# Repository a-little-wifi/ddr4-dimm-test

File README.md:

# DDR4-dimm-test

I need DDR4 UDIMMs for some PCs I got but I don't feel like buying any so I'll make it myself and harvest chips from a dead 32GB RDIMM (nevermind that's not possible, the RDIMM uses 4-bit chips and I need 8-bit chips)

Resources used:

- https://github.com/vmetodiev/OpenDIMM
- https://github.com/DiodeRed/kicad-footprint-ddr4-dimm
- Random motherboard schematics
- DDR4 specification

for future sodimm version?? :3
- https://github.com/Wallbraker/SODIMM

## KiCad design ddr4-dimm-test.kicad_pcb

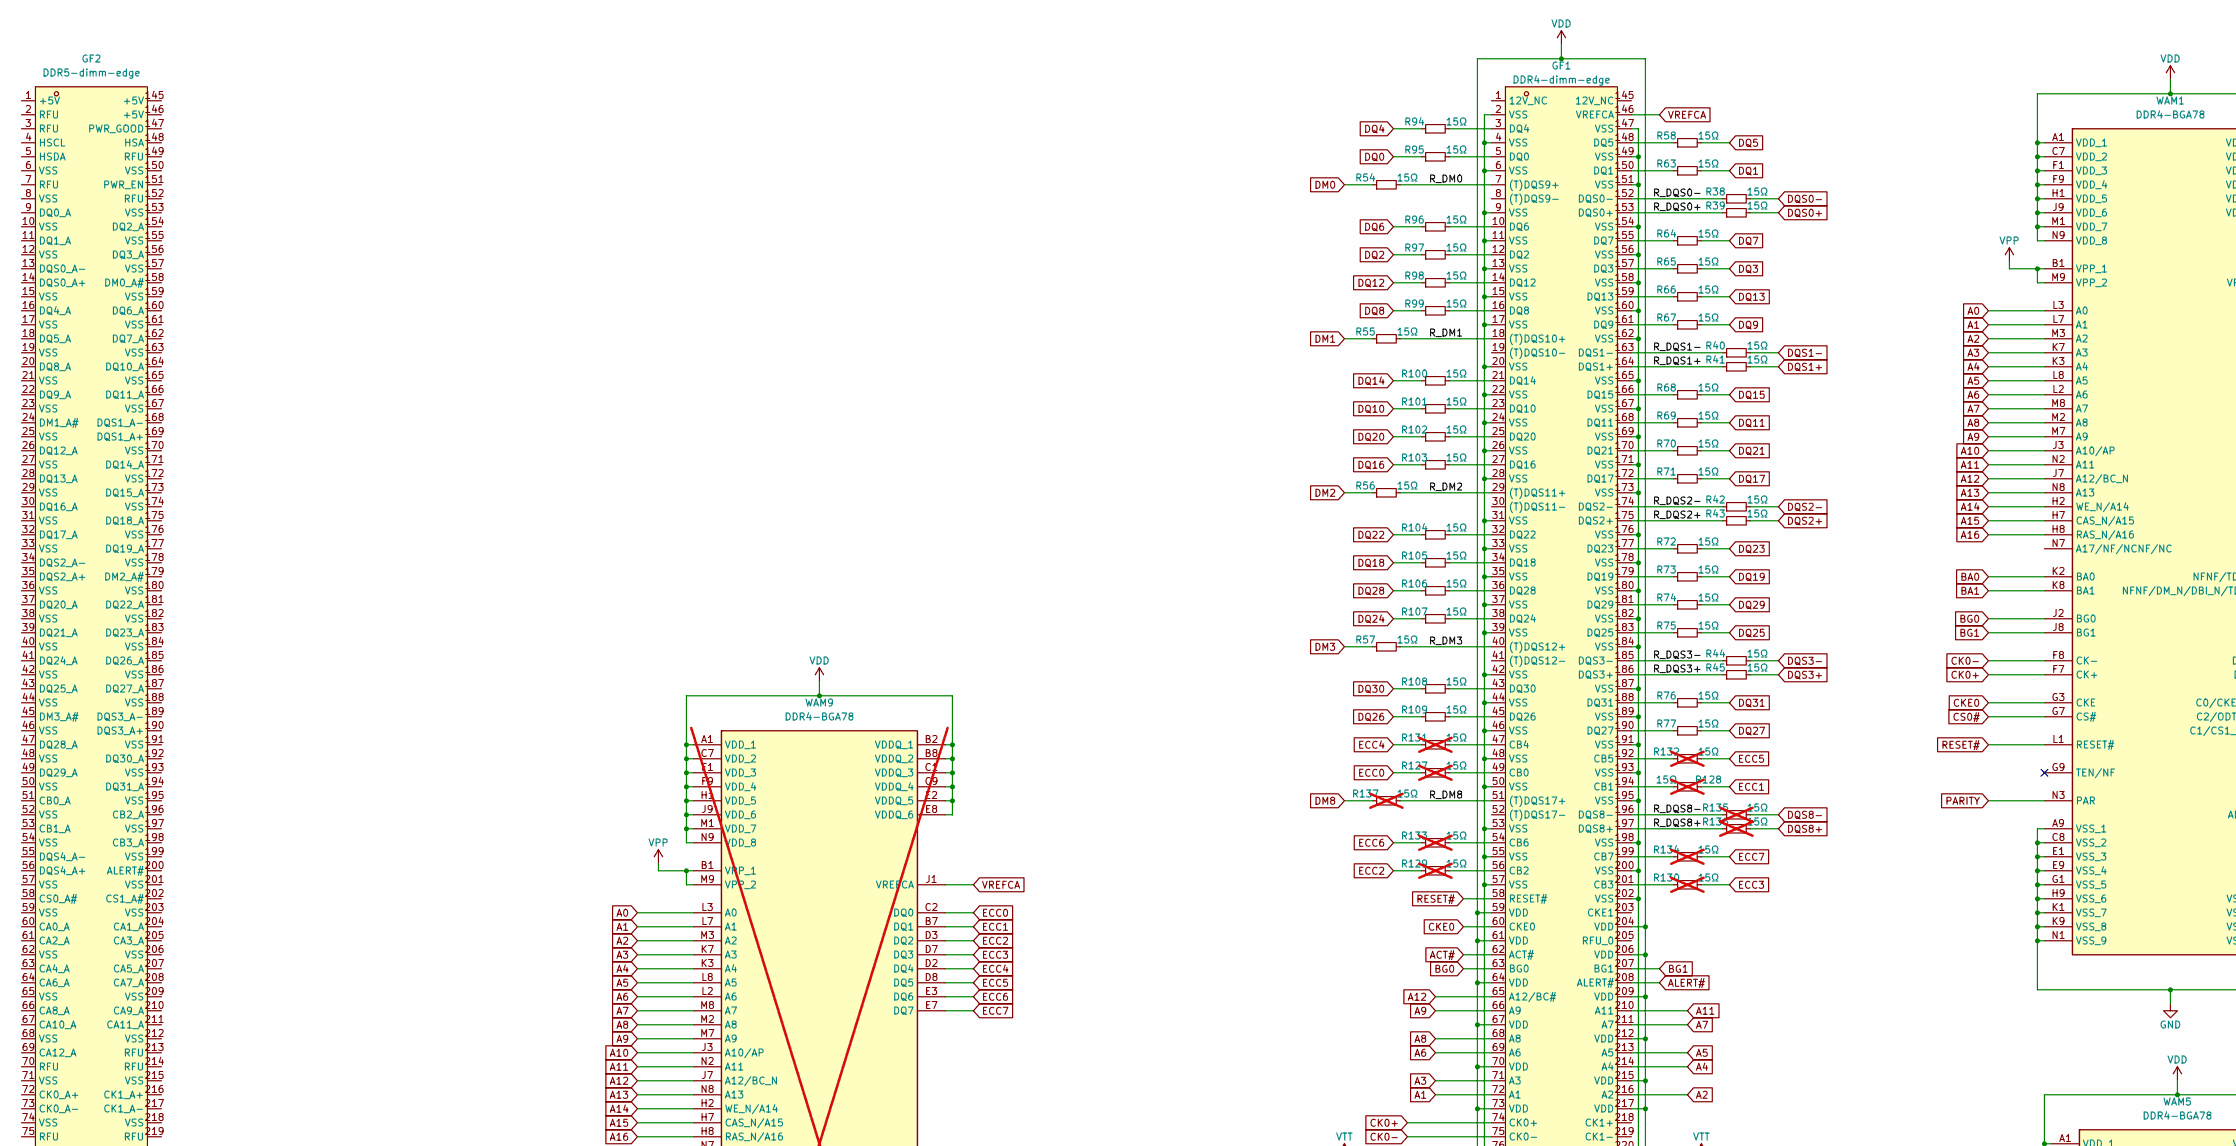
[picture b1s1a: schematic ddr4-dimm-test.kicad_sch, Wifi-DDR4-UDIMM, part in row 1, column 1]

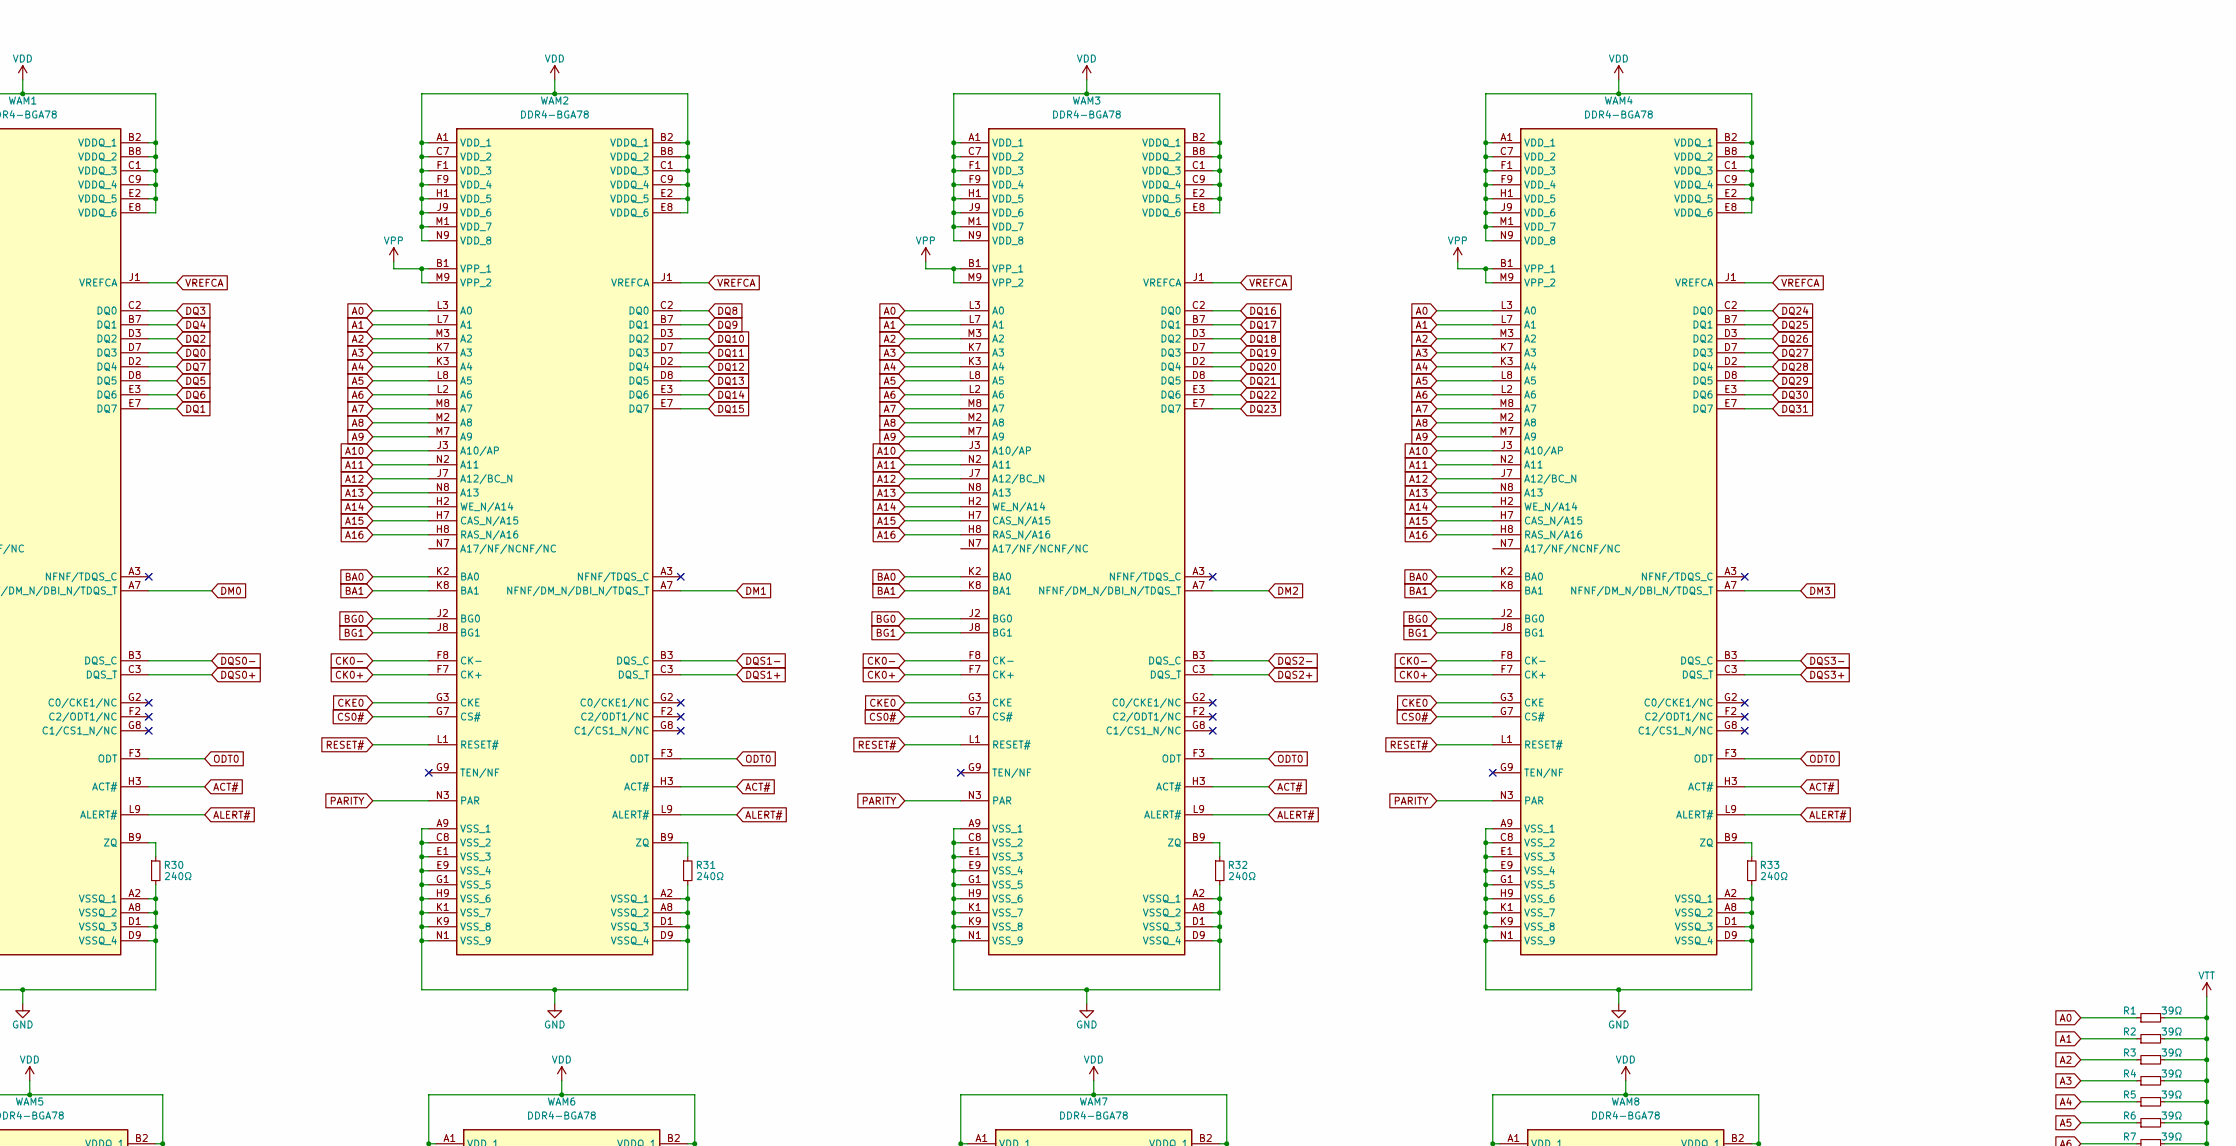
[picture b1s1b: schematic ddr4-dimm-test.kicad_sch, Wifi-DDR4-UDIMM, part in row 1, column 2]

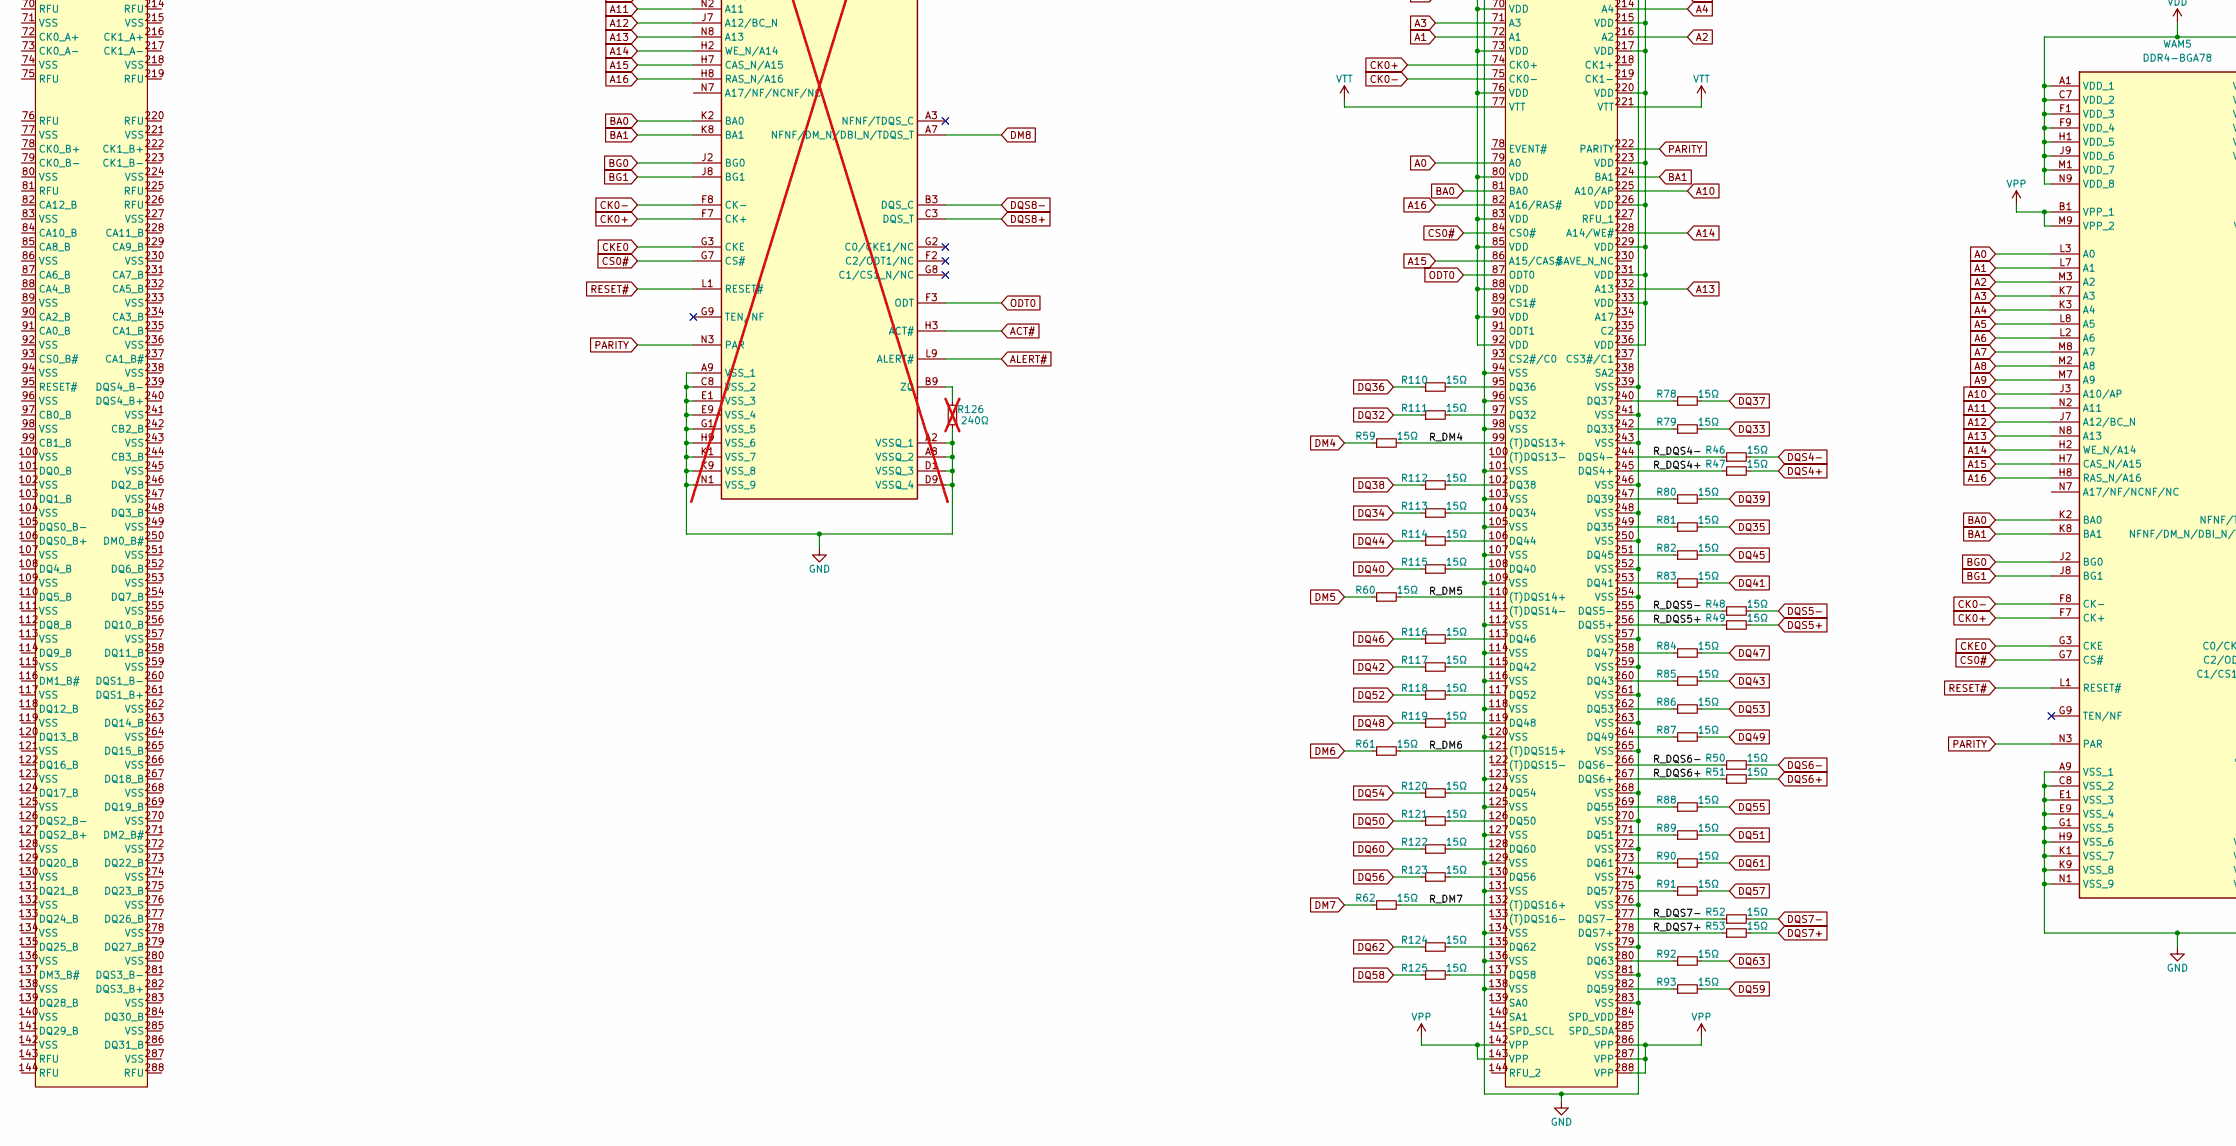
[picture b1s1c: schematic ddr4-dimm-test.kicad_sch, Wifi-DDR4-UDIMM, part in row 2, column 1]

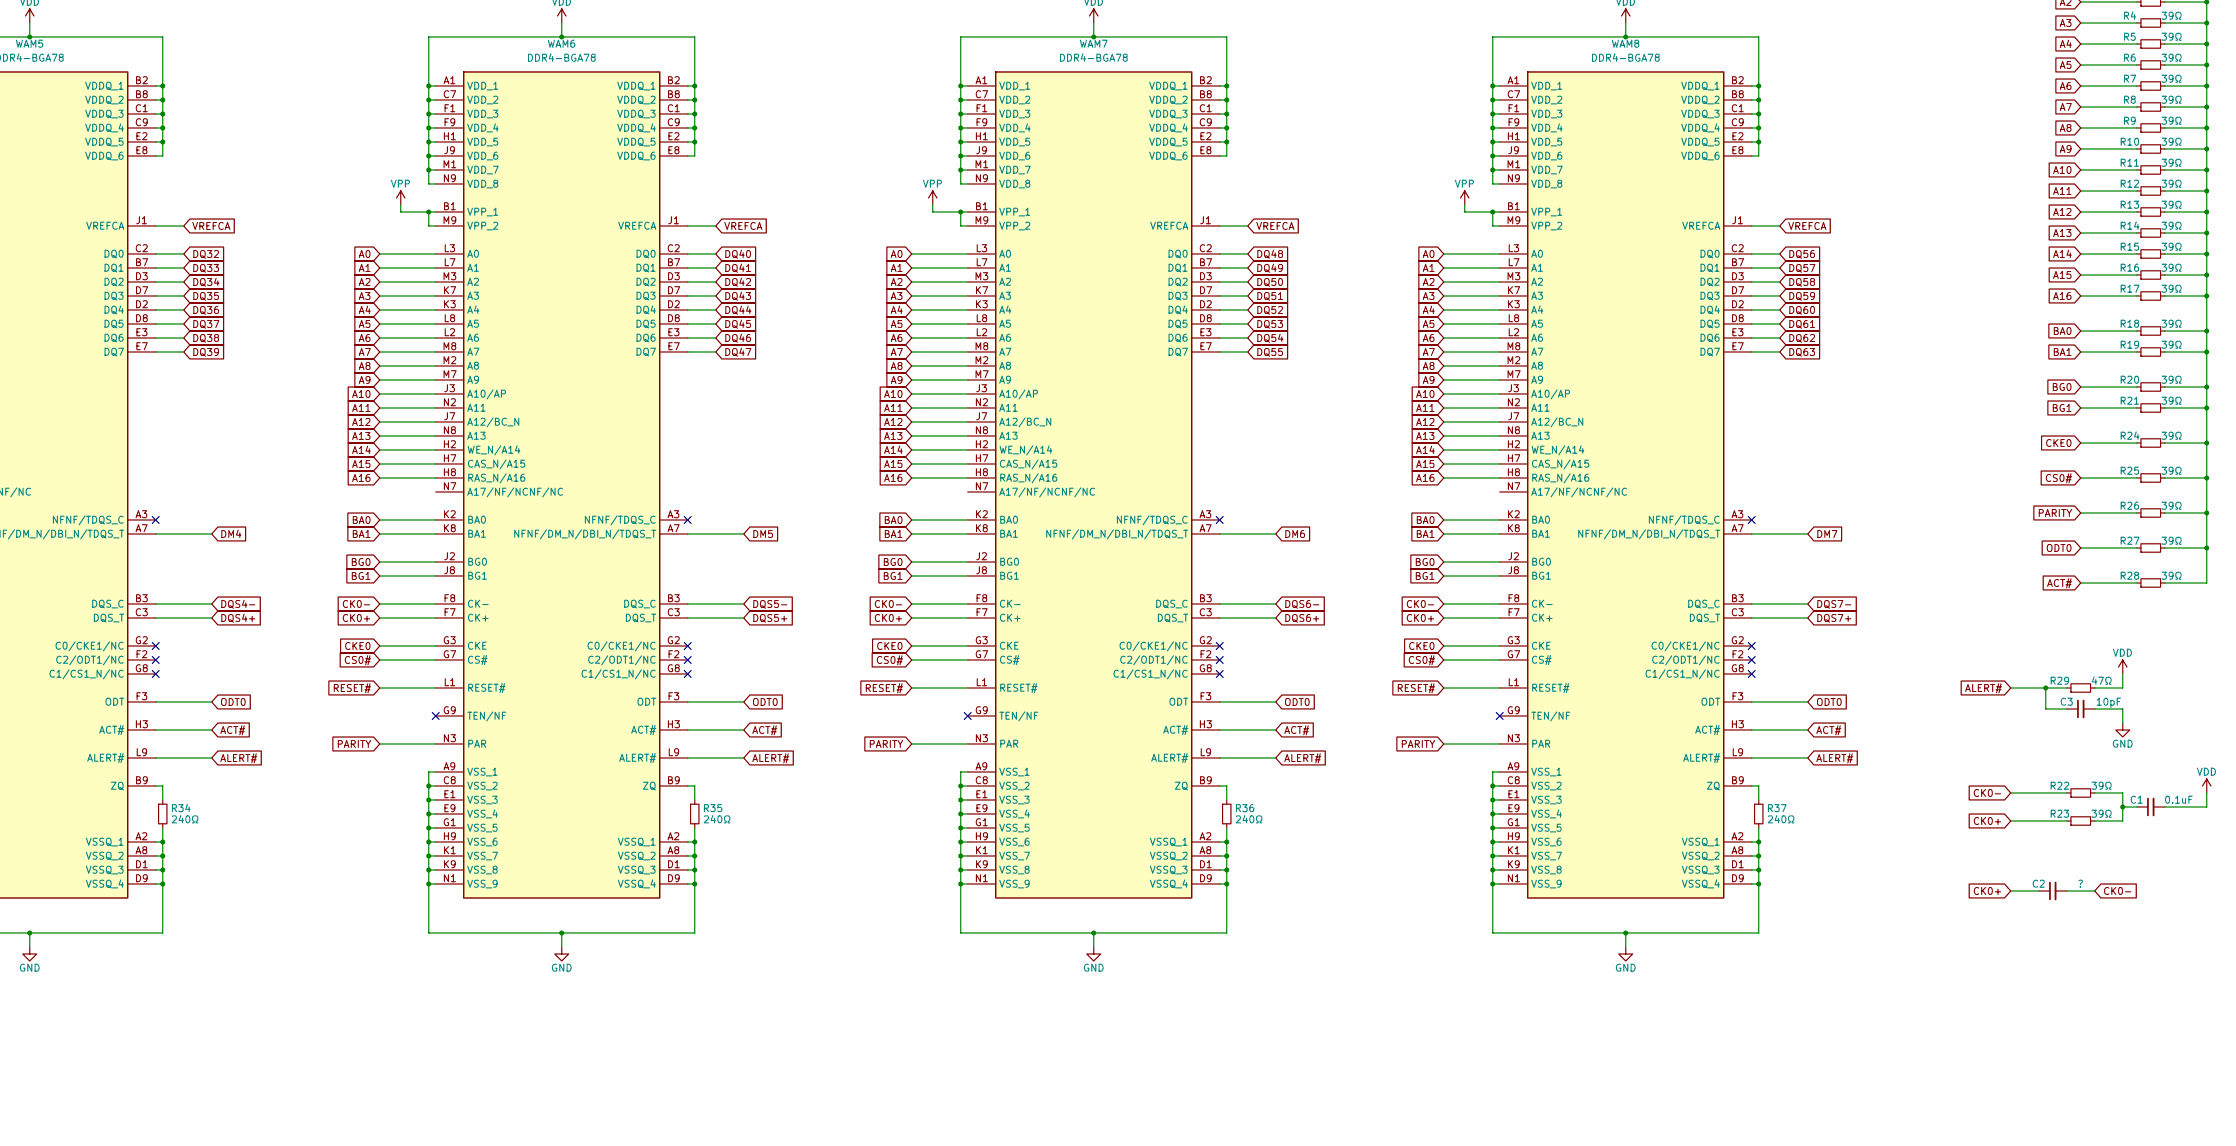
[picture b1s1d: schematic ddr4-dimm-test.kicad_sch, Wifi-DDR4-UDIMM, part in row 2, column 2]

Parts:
C1: 0.1uF; C_0402_1005Metric
C2: ?; C_0402_1005Metric
C3: 10pF; C_0402_1005Metric
GF1: DDR4-dimm-edge; DDR4-dimm
GF2: DDR5-dimm-edge
R1, R2, R3, R4, R5, R6, R7, R8, R9, R10, R11, R12, R13, R14, R15, R16, R17, R18, R19, R20, R21, R22, R23, R24, R25, R26, R27, R28: 39Ω; R_0402_1005Metric
R29: 47Ω; R_0402_1005Metric
R30, R31, R32, R33, R34, R35, R36, R37: 240Ω; R_0402_1005Metric
R38, R39, R40, R41, R42, R43, R44, R45, R46, R47, R48, R49, R50, R51, R52, R53, R54, R55, R56, R57, R58, R59, R60, R61, R62, R63, R64, R65, R66, R67, R68, R69, R70, R71, R72, R73, R74, R75, R76, R77, R78, R79, R80, R81, R82, R83, R84, R85, R86, R87, R88, R89, R90, R91, R92, R93, R94, R95, R96, R97, R98, R99, R100, R101, R102, R103, R104, R105, R106, R107, R108, R109, R110, R111, R112, R113, R114, R115, R116, R117, R118, R119, R120, R121, R122, R123, R124, R125: 15Ω; R_0402_1005Metric
R126: 240Ω; R_0402_1005Metric; not fitted
R127, R128, R129, R130, R131, R132, R133, R134, R135, R136, R137: 15Ω; R_0402_1005Metric; not fitted
WAM1, WAM2, WAM3, WAM4, WAM5, WAM6, WAM7, WAM8: DDR4-BGA78; Mouser Part Number 340-499666-TRAY
WAM9: DDR4-BGA78; Mouser Part Number 340-499666-TRAY; not fitted

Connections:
/R_DM0: GF1.7 ((T)DQS9+), R54.2
/R_DM1: GF1.18 ((T)DQS10+), R55.2
/R_DM2: GF1.29 ((T)DQS11+), R56.2
/R_DM3: GF1.40 ((T)DQS12+), R57.2
/R_DM4: GF1.99 ((T)DQS13+), R59.2
/R_DM5: GF1.110 ((T)DQS14+), R60.2
/R_DM6: GF1.121 ((T)DQS15+), R61.2
/R_DM7: GF1.132 ((T)DQS16+), R62.2
/R_DM8: GF1.51 ((T)DQS17+), R137.2
/R_DQS0+: GF1.153 (DQS0+), R39.1
/R_DQS0-: GF1.152 (DQS0-), R38.1
/R_DQS1+: GF1.164 (DQS1+), R41.1
/R_DQS1-: GF1.163 (DQS1-), R40.1
/R_DQS2+: GF1.175 (DQS2+), R43.1
/R_DQS2-: GF1.174 (DQS2-), R42.1
/R_DQS3+: GF1.186 (DQS3+), R45.1
/R_DQS3-: GF1.185 (DQS3-), R44.1
/R_DQS4+: GF1.245 (DQS4+), R47.1
/R_DQS4-: GF1.244 (DQS4-), R46.1
/R_DQS5+: GF1.256 (DQS5+), R49.1
/R_DQS5-: GF1.255 (DQS5-), R48.1
/R_DQS6+: GF1.267 (DQS6+), R51.1
/R_DQS6-: GF1.266 (DQS6-), R50.1
/R_DQS7+: GF1.278 (DQS7+), R53.1
/R_DQS7-: GF1.277 (DQS7-), R52.1
/R_DQS8+: GF1.197 (DQS8+), R136.1
/R_DQS8-: GF1.196 (DQS8-), R135.1
A0: GF1.79 (A0), R1.1, WAM1.L3 (A0), WAM2.L3 (A0), WAM3.L3 (A0), WAM4.L3 (A0), WAM5.L3 (A0), WAM6.L3 (A0), WAM7.L3 (A0), WAM8.L3 (A0), WAM9.L3 (A0)
A1: GF1.72 (A1), R2.1, WAM1.L7 (A1), WAM2.L7 (A1), WAM3.L7 (A1), WAM4.L7 (A1), WAM5.L7 (A1), WAM6.L7 (A1), WAM7.L7 (A1), WAM8.L7 (A1), WAM9.L7 (A1)
A2: GF1.216 (A2), R3.1, WAM1.M3 (A2), WAM2.M3 (A2), WAM3.M3 (A2), WAM4.M3 (A2), WAM5.M3 (A2), WAM6.M3 (A2), WAM7.M3 (A2), WAM8.M3 (A2), WAM9.M3 (A2)
A3: GF1.71 (A3), R4.1, WAM1.K7 (A3), WAM2.K7 (A3), WAM3.K7 (A3), WAM4.K7 (A3), WAM5.K7 (A3), WAM6.K7 (A3), WAM7.K7 (A3), WAM8.K7 (A3), WAM9.K7 (A3)
A4: GF1.214 (A4), R5.1, WAM1.K3 (A4), WAM2.K3 (A4), WAM3.K3 (A4), WAM4.K3 (A4), WAM5.K3 (A4), WAM6.K3 (A4), WAM7.K3 (A4), WAM8.K3 (A4), WAM9.K3 (A4)
A5: GF1.213 (A5), R6.1, WAM1.L8 (A5), WAM2.L8 (A5), WAM3.L8 (A5), WAM4.L8 (A5), WAM5.L8 (A5), WAM6.L8 (A5), WAM7.L8 (A5), WAM8.L8 (A5), WAM9.L8 (A5)
A6: GF1.69 (A6), R7.1, WAM1.L2 (A6), WAM2.L2 (A6), WAM3.L2 (A6), WAM4.L2 (A6), WAM5.L2 (A6), WAM6.L2 (A6), WAM7.L2 (A6), WAM8.L2 (A6), WAM9.L2 (A6)
A7: GF1.211 (A7), R8.1, WAM1.M8 (A7), WAM2.M8 (A7), WAM3.M8 (A7), WAM4.M8 (A7), WAM5.M8 (A7), WAM6.M8 (A7), WAM7.M8 (A7), WAM8.M8 (A7), WAM9.M8 (A7)
A8: GF1.68 (A8), R9.1, WAM1.M2 (A8), WAM2.M2 (A8), WAM3.M2 (A8), WAM4.M2 (A8), WAM5.M2 (A8), WAM6.M2 (A8), WAM7.M2 (A8), WAM8.M2 (A8), WAM9.M2 (A8)
A9: GF1.66 (A9), R10.1, WAM1.M7 (A9), WAM2.M7 (A9), WAM3.M7 (A9), WAM4.M7 (A9), WAM5.M7 (A9), WAM6.M7 (A9), WAM7.M7 (A9), WAM8.M7 (A9), WAM9.M7 (A9)
A10: GF1.225 (A10/AP), R11.1, WAM1.J3 (A10/AP), WAM2.J3 (A10/AP), WAM3.J3 (A10/AP), WAM4.J3 (A10/AP), WAM5.J3 (A10/AP), WAM6.J3 (A10/AP), WAM7.J3 (A10/AP), WAM8.J3 (A10/AP), WAM9.J3 (A10/AP)
A11: GF1.210 (A11), R12.1, WAM1.N2 (A11), WAM2.N2 (A11), WAM3.N2 (A11), WAM4.N2 (A11), WAM5.N2 (A11), WAM6.N2 (A11), WAM7.N2 (A11), WAM8.N2 (A11), WAM9.N2 (A11)
A12: GF1.65 (A12/BC#), R13.1, WAM1.J7 (A12/BC_N), WAM2.J7 (A12/BC_N), WAM3.J7 (A12/BC_N), WAM4.J7 (A12/BC_N), WAM5.J7 (A12/BC_N), WAM6.J7 (A12/BC_N), WAM7.J7 (A12/BC_N), WAM8.J7 (A12/BC_N), WAM9.J7 (A12/BC_N)
A13: GF1.232 (A13), R14.1, WAM1.N8 (A13), WAM2.N8 (A13), WAM3.N8 (A13), WAM4.N8 (A13), WAM5.N8 (A13), WAM6.N8 (A13), WAM7.N8 (A13), WAM8.N8 (A13), WAM9.N8 (A13)
A14: GF1.228 (A14/WE#), R15.1, WAM1.H2 (WE_N/A14), WAM2.H2 (WE_N/A14), WAM3.H2 (WE_N/A14), WAM4.H2 (WE_N/A14), WAM5.H2 (WE_N/A14), WAM6.H2 (WE_N/A14), WAM7.H2 (WE_N/A14), WAM8.H2 (WE_N/A14), WAM9.H2 (WE_N/A14)
A15: GF1.86 (A15/CAS#), R16.1, WAM1.H7 (CAS_N/A15), WAM2.H7 (CAS_N/A15), WAM3.H7 (CAS_N/A15), WAM4.H7 (CAS_N/A15), WAM5.H7 (CAS_N/A15), WAM6.H7 (CAS_N/A15), WAM7.H7 (CAS_N/A15), WAM8.H7 (CAS_N/A15), WAM9.H7 (CAS_N/A15)
A16: GF1.82 (A16/RAS#), R17.1, WAM1.H8 (RAS_N/A16), WAM2.H8 (RAS_N/A16), WAM3.H8 (RAS_N/A16), WAM4.H8 (RAS_N/A16), WAM5.H8 (RAS_N/A16), WAM6.H8 (RAS_N/A16), WAM7.H8 (RAS_N/A16), WAM8.H8 (RAS_N/A16), WAM9.H8 (RAS_N/A16)
ACT#: GF1.62 (ACT#), R28.1, WAM1.H3 (ACT#), WAM2.H3 (ACT#), WAM3.H3 (ACT#), WAM4.H3 (ACT#), WAM5.H3 (ACT#), WAM6.H3 (ACT#), WAM7.H3 (ACT#), WAM8.H3 (ACT#), WAM9.H3 (ACT#)
ALERT#: C3.1, GF1.208 (ALERT#), R29.1, WAM1.L9 (ALERT#), WAM2.L9 (ALERT#), WAM3.L9 (ALERT#), WAM4.L9 (ALERT#), WAM5.L9 (ALERT#), WAM6.L9 (ALERT#), WAM7.L9 (ALERT#), WAM8.L9 (ALERT#), WAM9.L9 (ALERT#)
BA0: GF1.81 (BA0), R18.1, WAM1.K2 (BA0), WAM2.K2 (BA0), WAM3.K2 (BA0), WAM4.K2 (BA0), WAM5.K2 (BA0), WAM6.K2 (BA0), WAM7.K2 (BA0), WAM8.K2 (BA0), WAM9.K2 (BA0)
BA1: GF1.224 (BA1), R19.1, WAM1.K8 (BA1), WAM2.K8 (BA1), WAM3.K8 (BA1), WAM4.K8 (BA1), WAM5.K8 (BA1), WAM6.K8 (BA1), WAM7.K8 (BA1), WAM8.K8 (BA1), WAM9.K8 (BA1)
BG0: GF1.63 (BG0), R20.1, WAM1.J2 (BG0), WAM2.J2 (BG0), WAM3.J2 (BG0), WAM4.J2 (BG0), WAM5.J2 (BG0), WAM6.J2 (BG0), WAM7.J2 (BG0), WAM8.J2 (BG0), WAM9.J2 (BG0)
BG1: GF1.207 (BG1), R21.1, WAM1.J8 (BG1), WAM2.J8 (BG1), WAM3.J8 (BG1), WAM4.J8 (BG1), WAM5.J8 (BG1), WAM6.J8 (BG1), WAM7.J8 (BG1), WAM8.J8 (BG1), WAM9.J8 (BG1)
CK0+: C2.1, GF1.74 (CK0+), R23.1, WAM1.F7 (CK+), WAM2.F7 (CK+), WAM3.F7 (CK+), WAM4.F7 (CK+), WAM5.F7 (CK+), WAM6.F7 (CK+), WAM7.F7 (CK+), WAM8.F7 (CK+), WAM9.F7 (CK+)
CK0-: C2.2, GF1.75 (CK0-), R22.1, WAM1.F8 (CK-), WAM2.F8 (CK-), WAM3.F8 (CK-), WAM4.F8 (CK-), WAM5.F8 (CK-), WAM6.F8 (CK-), WAM7.F8 (CK-), WAM8.F8 (CK-), WAM9.F8 (CK-)
CKE0: GF1.60 (CKE0), R24.1, WAM1.G3 (CKE), WAM2.G3 (CKE), WAM3.G3 (CKE), WAM4.G3 (CKE), WAM5.G3 (CKE), WAM6.G3 (CKE), WAM7.G3 (CKE), WAM8.G3 (CKE), WAM9.G3 (CKE)
CS0#: GF1.84 (CS0#), R25.1, WAM1.G7 (CS#), WAM2.G7 (CS#), WAM3.G7 (CS#), WAM4.G7 (CS#), WAM5.G7 (CS#), WAM6.G7 (CS#), WAM7.G7 (CS#), WAM8.G7 (CS#), WAM9.G7 (CS#)
DM0: R54.1, WAM1.A7 (NFNF/DM_N/DBI_N/TDQS_T)
DM1: R55.1, WAM2.A7 (NFNF/DM_N/DBI_N/TDQS_T)
DM2: R56.1, WAM3.A7 (NFNF/DM_N/DBI_N/TDQS_T)
DM3: R57.1, WAM4.A7 (NFNF/DM_N/DBI_N/TDQS_T)
DM4: R59.1, WAM5.A7 (NFNF/DM_N/DBI_N/TDQS_T)
DM5: R60.1, WAM6.A7 (NFNF/DM_N/DBI_N/TDQS_T)
DM6: R61.1, WAM7.A7 (NFNF/DM_N/DBI_N/TDQS_T)
DM7: R62.1, WAM8.A7 (NFNF/DM_N/DBI_N/TDQS_T)
DM8: R137.1, WAM9.A7 (NFNF/DM_N/DBI_N/TDQS_T)
DQ0: R95.1, WAM1.D7 (DQ3)
DQ1: R63.2, WAM1.E7 (DQ7)
DQ2: R97.1, WAM1.D3 (DQ2)
DQ3: R65.2, WAM1.C2 (DQ0)
DQ4: R94.1, WAM1.B7 (DQ1)
DQ5: R58.2, WAM1.D8 (DQ5)
DQ6: R96.1, WAM1.E3 (DQ6)
DQ7: R64.2, WAM1.D2 (DQ4)
DQ8: R99.1, WAM2.C2 (DQ0)
DQ9: R67.2, WAM2.B7 (DQ1)
DQ10: R101.1, WAM2.D3 (DQ2)
DQ11: R69.2, WAM2.D7 (DQ3)
DQ12: R98.1, WAM2.D2 (DQ4)
DQ13: R66.2, WAM2.D8 (DQ5)
DQ14: R100.1, WAM2.E3 (DQ6)
DQ15: R68.2, WAM2.E7 (DQ7)
DQ16: R103.1, WAM3.C2 (DQ0)
DQ17: R71.2, WAM3.B7 (DQ1)
DQ18: R105.1, WAM3.D3 (DQ2)
DQ19: R73.2, WAM3.D7 (DQ3)
DQ20: R102.1, WAM3.D2 (DQ4)
DQ21: R70.2, WAM3.D8 (DQ5)
DQ22: R104.1, WAM3.E3 (DQ6)
DQ23: R72.2, WAM3.E7 (DQ7)
DQ24: R107.1, WAM4.C2 (DQ0)
DQ25: R75.2, WAM4.B7 (DQ1)
DQ26: R109.1, WAM4.D3 (DQ2)
DQ27: R77.2, WAM4.D7 (DQ3)
DQ28: R106.1, WAM4.D2 (DQ4)
DQ29: R74.2, WAM4.D8 (DQ5)
DQ30: R108.1, WAM4.E3 (DQ6)
DQ31: R76.2, WAM4.E7 (DQ7)
DQ32: R111.1, WAM5.C2 (DQ0)
DQ33: R79.2, WAM5.B7 (DQ1)
DQ34: R113.1, WAM5.D3 (DQ2)
DQ35: R81.2, WAM5.D7 (DQ3)
DQ36: R110.1, WAM5.D2 (DQ4)
DQ37: R78.2, WAM5.D8 (DQ5)
DQ38: R112.1, WAM5.E3 (DQ6)
DQ39: R80.2, WAM5.E7 (DQ7)
DQ40: R115.1, WAM6.C2 (DQ0)
DQ41: R83.2, WAM6.B7 (DQ1)
DQ42: R117.1, WAM6.D3 (DQ2)
DQ43: R85.2, WAM6.D7 (DQ3)
DQ44: R114.1, WAM6.D2 (DQ4)
DQ45: R82.2, WAM6.D8 (DQ5)
DQ46: R116.1, WAM6.E3 (DQ6)
DQ47: R84.2, WAM6.E7 (DQ7)
DQ48: R119.1, WAM7.C2 (DQ0)
DQ49: R87.2, WAM7.B7 (DQ1)
DQ50: R121.1, WAM7.D3 (DQ2)
DQ51: R89.2, WAM7.D7 (DQ3)
DQ52: R118.1, WAM7.D2 (DQ4)
DQ53: R86.2, WAM7.D8 (DQ5)
DQ54: R120.1, WAM7.E3 (DQ6)
DQ55: R88.2, WAM7.E7 (DQ7)
DQ56: R123.1, WAM8.C2 (DQ0)
DQ57: R91.2, WAM8.B7 (DQ1)
DQ58: R125.1, WAM8.D3 (DQ2)
DQ59: R93.2, WAM8.D7 (DQ3)
DQ60: R122.1, WAM8.D2 (DQ4)
DQ61: R90.2, WAM8.D8 (DQ5)
DQ62: R124.1, WAM8.E3 (DQ6)
DQ63: R92.2, WAM8.E7 (DQ7)
DQS0+: R39.2, WAM1.C3 (DQS_T)
DQS0-: R38.2, WAM1.B3 (DQS_C)
DQS1+: R41.2, WAM2.C3 (DQS_T)
DQS1-: R40.2, WAM2.B3 (DQS_C)
DQS2+: R43.2, WAM3.C3 (DQS_T)
DQS2-: R42.2, WAM3.B3 (DQS_C)
DQS3+: R45.2, WAM4.C3 (DQS_T)
DQS3-: R44.2, WAM4.B3 (DQS_C)
DQS4+: R47.2, WAM5.C3 (DQS_T)
DQS4-: R46.2, WAM5.B3 (DQS_C)
DQS5+: R49.2, WAM6.C3 (DQS_T)
DQS5-: R48.2, WAM6.B3 (DQS_C)
DQS6+: R51.2, WAM7.C3 (DQS_T)
DQS6-: R50.2, WAM7.B3 (DQS_C)
DQS7+: R53.2, WAM8.C3 (DQS_T)
DQS7-: R52.2, WAM8.B3 (DQS_C)
DQS8+: R136.2, WAM9.C3 (DQS_T)
DQS8-: R135.2, WAM9.B3 (DQS_C)
ECC0: R127.1, WAM9.C2 (DQ0)
ECC1: R128.1, WAM9.B7 (DQ1)
ECC2: R129.1, WAM9.D3 (DQ2)
ECC3: R130.2, WAM9.D7 (DQ3)
ECC4: R131.1, WAM9.D2 (DQ4)
ECC5: R132.2, WAM9.D8 (DQ5)
ECC6: R133.1, WAM9.E3 (DQ6)
ECC7: R134.2, WAM9.E7 (DQ7)
GND: C3.2, GF1.2 (VSS), GF1.4 (VSS), GF1.6 (VSS), GF1.9 (VSS), GF1.11 (VSS), GF1.13 (VSS), GF1.15 (VSS), GF1.17 (VSS), GF1.20 (VSS), GF1.22 (VSS), GF1.24 (VSS), GF1.26 (VSS), GF1.28 (VSS), GF1.31 (VSS), GF1.33 (VSS), GF1.35 (VSS), GF1.37 (VSS), GF1.39 (VSS), GF1.42 (VSS), GF1.44 (VSS), GF1.46 (VSS), GF1.48 (VSS), GF1.50 (VSS), GF1.53 (VSS), GF1.55 (VSS), GF1.57 (VSS), GF1.94 (VSS), GF1.96 (VSS), GF1.98 (VSS), GF1.101 (VSS), GF1.103 (VSS), GF1.105 (VSS), GF1.107 (VSS), GF1.109 (VSS), GF1.112 (VSS), GF1.114 (VSS), GF1.116 (VSS), GF1.118 (VSS), GF1.120 (VSS), GF1.123 (VSS), GF1.125 (VSS), GF1.127 (VSS), GF1.129 (VSS), GF1.131 (VSS), GF1.134 (VSS), GF1.136 (VSS), GF1.138 (VSS), GF1.147 (VSS), GF1.149 (VSS), GF1.151 (VSS), GF1.154 (VSS), GF1.156 (VSS), GF1.158 (VSS), GF1.160 (VSS), GF1.162 (VSS), GF1.165 (VSS), GF1.167 (VSS), GF1.169 (VSS), GF1.171 (VSS), GF1.173 (VSS), GF1.176 (VSS), GF1.178 (VSS), GF1.180 (VSS), GF1.182 (VSS), GF1.184 (VSS), GF1.187 (VSS), GF1.189 (VSS), GF1.191 (VSS), GF1.193 (VSS), GF1.195 (VSS), GF1.198 (VSS), GF1.200 (VSS), GF1.202 (VSS), GF1.239 (VSS), GF1.241 (VSS), GF1.243 (VSS), GF1.246 (VSS), GF1.248 (VSS), GF1.250 (VSS), GF1.252 (VSS), GF1.254 (VSS), GF1.257 (VSS), GF1.259 (VSS), GF1.261 (VSS), GF1.263 (VSS), GF1.265 (VSS), GF1.268 (VSS), GF1.270 (VSS), GF1.272 (VSS), GF1.274 (VSS), GF1.276 (VSS), GF1.279 (VSS), GF1.281 (VSS), GF1.283 (VSS), R30.2, R31.2, R32.2, R33.2, R34.2, R35.2, R36.2, R37.2, R126.2, WAM1.A2 (VSSQ_1), WAM1.A8 (VSSQ_2), WAM1.A9 (VSS_1), WAM1.C8 (VSS_2), WAM1.D1 (VSSQ_3), WAM1.D9 (VSSQ_4), WAM1.E1 (VSS_3), WAM1.E9 (VSS_4), WAM1.G1 (VSS_5), WAM1.H9 (VSS_6), WAM1.K1 (VSS_7), WAM1.K9 (VSS_8), WAM1.N1 (VSS_9), WAM2.A2 (VSSQ_1), WAM2.A8 (VSSQ_2), WAM2.A9 (VSS_1), WAM2.C8 (VSS_2), WAM2.D1 (VSSQ_3), WAM2.D9 (VSSQ_4), WAM2.E1 (VSS_3), WAM2.E9 (VSS_4), WAM2.G1 (VSS_5), WAM2.H9 (VSS_6), WAM2.K1 (VSS_7), WAM2.K9 (VSS_8), WAM2.N1 (VSS_9), WAM3.A2 (VSSQ_1), WAM3.A8 (VSSQ_2), WAM3.A9 (VSS_1), WAM3.C8 (VSS_2), WAM3.D1 (VSSQ_3), WAM3.D9 (VSSQ_4), WAM3.E1 (VSS_3), WAM3.E9 (VSS_4), WAM3.G1 (VSS_5), WAM3.H9 (VSS_6), WAM3.K1 (VSS_7), WAM3.K9 (VSS_8), WAM3.N1 (VSS_9), WAM4.A2 (VSSQ_1), WAM4.A8 (VSSQ_2), WAM4.A9 (VSS_1), WAM4.C8 (VSS_2), WAM4.D1 (VSSQ_3), WAM4.D9 (VSSQ_4), WAM4.E1 (VSS_3), WAM4.E9 (VSS_4), WAM4.G1 (VSS_5), WAM4.H9 (VSS_6), WAM4.K1 (VSS_7), WAM4.K9 (VSS_8), WAM4.N1 (VSS_9), WAM5.A2 (VSSQ_1), WAM5.A8 (VSSQ_2), WAM5.A9 (VSS_1), WAM5.C8 (VSS_2), WAM5.D1 (VSSQ_3), WAM5.D9 (VSSQ_4), WAM5.E1 (VSS_3), WAM5.E9 (VSS_4), WAM5.G1 (VSS_5), WAM5.H9 (VSS_6), WAM5.K1 (VSS_7), WAM5.K9 (VSS_8), WAM5.N1 (VSS_9), WAM6.A2 (VSSQ_1), WAM6.A8 (VSSQ_2), WAM6.A9 (VSS_1), WAM6.C8 (VSS_2), WAM6.D1 (VSSQ_3), WAM6.D9 (VSSQ_4), WAM6.E1 (VSS_3), WAM6.E9 (VSS_4), WAM6.G1 (VSS_5), WAM6.H9 (VSS_6), WAM6.K1 (VSS_7), WAM6.K9 (VSS_8), WAM6.N1 (VSS_9), WAM7.A2 (VSSQ_1), WAM7.A8 (VSSQ_2), WAM7.A9 (VSS_1), WAM7.C8 (VSS_2), WAM7.D1 (VSSQ_3), WAM7.D9 (VSSQ_4), WAM7.E1 (VSS_3), WAM7.E9 (VSS_4), WAM7.G1 (VSS_5), WAM7.H9 (VSS_6), WAM7.K1 (VSS_7), WAM7.K9 (VSS_8), WAM7.N1 (VSS_9), WAM8.A2 (VSSQ_1), WAM8.A8 (VSSQ_2), WAM8.A9 (VSS_1), WAM8.C8 (VSS_2), WAM8.D1 (VSSQ_3), WAM8.D9 (VSSQ_4), WAM8.E1 (VSS_3), WAM8.E9 (VSS_4), WAM8.G1 (VSS_5), WAM8.H9 (VSS_6), WAM8.K1 (VSS_7), WAM8.K9 (VSS_8), WAM8.N1 (VSS_9), WAM9.A2 (VSSQ_1), WAM9.A8 (VSSQ_2), WAM9.A9 (VSS_1), WAM9.C8 (VSS_2), WAM9.D1 (VSSQ_3), WAM9.D9 (VSSQ_4), WAM9.E1 (VSS_3), WAM9.E9 (VSS_4), WAM9.G1 (VSS_5), WAM9.H9 (VSS_6), WAM9.K1 (VSS_7), WAM9.K9 (VSS_8), WAM9.N1 (VSS_9)
unnamed: C1.1, R22.2, R23.2
unnamed: GF1.49 (CB0), R127.2
unnamed: GF1.194 (CB1), R128.2
unnamed: GF1.56 (CB2), R129.2
unnamed: GF1.201 (CB3), R130.1
unnamed: GF1.47 (CB4), R131.2
unnamed: GF1.192 (CB5), R132.1
unnamed: GF1.54 (CB6), R133.2
unnamed: GF1.199 (CB7), R134.1
unnamed: GF1.5 (DQ0), R95.2
unnamed: GF1.150 (DQ1), R63.1
unnamed: GF1.12 (DQ2), R97.2
unnamed: GF1.157 (DQ3), R65.1
unnamed: GF1.3 (DQ4), R94.2
unnamed: GF1.148 (DQ5), R58.1
unnamed: GF1.10 (DQ6), R96.2
unnamed: GF1.155 (DQ7), R64.1
unnamed: GF1.16 (DQ8), R99.2
unnamed: GF1.161 (DQ9), R67.1
unnamed: GF1.23 (DQ10), R101.2
unnamed: GF1.168 (DQ11), R69.1
unnamed: GF1.14 (DQ12), R98.2
unnamed: GF1.159 (DQ13), R66.1
unnamed: GF1.21 (DQ14), R100.2
unnamed: GF1.166 (DQ15), R68.1
unnamed: GF1.27 (DQ16), R103.2
unnamed: GF1.172 (DQ17), R71.1
unnamed: GF1.34 (DQ18), R105.2
unnamed: GF1.179 (DQ19), R73.1
unnamed: GF1.25 (DQ20), R102.2
unnamed: GF1.170 (DQ21), R70.1
unnamed: GF1.32 (DQ22), R104.2
unnamed: GF1.177 (DQ23), R72.1
unnamed: GF1.38 (DQ24), R107.2
unnamed: GF1.183 (DQ25), R75.1
unnamed: GF1.45 (DQ26), R109.2
unnamed: GF1.190 (DQ27), R77.1
unnamed: GF1.36 (DQ28), R106.2
unnamed: GF1.181 (DQ29), R74.1
unnamed: GF1.43 (DQ30), R108.2
unnamed: GF1.188 (DQ31), R76.1
unnamed: GF1.97 (DQ32), R111.2
unnamed: GF1.242 (DQ33), R79.1
unnamed: GF1.104 (DQ34), R113.2
unnamed: GF1.249 (DQ35), R81.1
unnamed: GF1.95 (DQ36), R110.2
unnamed: GF1.240 (DQ37), R78.1
unnamed: GF1.102 (DQ38), R112.2
unnamed: GF1.247 (DQ39), R80.1
unnamed: GF1.108 (DQ40), R115.2
unnamed: GF1.253 (DQ41), R83.1
unnamed: GF1.115 (DQ42), R117.2
unnamed: GF1.260 (DQ43), R85.1
unnamed: GF1.106 (DQ44), R114.2
unnamed: GF1.251 (DQ45), R82.1
unnamed: GF1.113 (DQ46), R116.2
unnamed: GF1.258 (DQ47), R84.1
unnamed: GF1.119 (DQ48), R119.2
unnamed: GF1.264 (DQ49), R87.1
unnamed: GF1.126 (DQ50), R121.2
unnamed: GF1.271 (DQ51), R89.1
unnamed: GF1.117 (DQ52), R118.2
unnamed: GF1.262 (DQ53), R86.1
unnamed: GF1.124 (DQ54), R120.2
unnamed: GF1.269 (DQ55), R88.1
unnamed: GF1.130 (DQ56), R123.2
unnamed: GF1.275 (DQ57), R91.1
unnamed: GF1.137 (DQ58), R125.2
unnamed: GF1.282 (DQ59), R93.1
unnamed: GF1.128 (DQ60), R122.2
unnamed: GF1.273 (DQ61), R90.1
unnamed: GF1.135 (DQ62), R124.2
unnamed: GF1.280 (DQ63), R92.1
unnamed: R30.1, WAM1.B9 (ZQ)
unnamed: R31.1, WAM2.B9 (ZQ)
unnamed: R32.1, WAM3.B9 (ZQ)
unnamed: R33.1, WAM4.B9 (ZQ)
unnamed: R34.1, WAM5.B9 (ZQ)
unnamed: R35.1, WAM6.B9 (ZQ)
unnamed: R36.1, WAM7.B9 (ZQ)
unnamed: R37.1, WAM8.B9 (ZQ)
unnamed: R126.1, WAM9.B9 (ZQ)
ODT0: GF1.87 (ODT0), R27.1, WAM1.F3 (ODT), WAM2.F3 (ODT), WAM3.F3 (ODT), WAM4.F3 (ODT), WAM5.F3 (ODT), WAM6.F3 (ODT), WAM7.F3 (ODT), WAM8.F3 (ODT), WAM9.F3 (ODT)
PARITY: GF1.222 (PARITY), R26.1, WAM1.N3 (PAR), WAM2.N3 (PAR), WAM3.N3 (PAR), WAM4.N3 (PAR), WAM5.N3 (PAR), WAM6.N3 (PAR), WAM7.N3 (PAR), WAM8.N3 (PAR), WAM9.N3 (PAR)
RESET#: GF1.58 (RESET#), WAM1.L1 (RESET#), WAM2.L1 (RESET#), WAM3.L1 (RESET#), WAM4.L1 (RESET#), WAM5.L1 (RESET#), WAM6.L1 (RESET#), WAM7.L1 (RESET#), WAM8.L1 (RESET#), WAM9.L1 (RESET#)
VDD: C1.2, GF1.59 (VDD), GF1.61 (VDD), GF1.64 (VDD), GF1.67 (VDD), GF1.70 (VDD), GF1.73 (VDD), GF1.76 (VDD), GF1.80 (VDD), GF1.83 (VDD), GF1.85 (VDD), GF1.88 (VDD), GF1.90 (VDD), GF1.92 (VDD), GF1.204 (VDD), GF1.206 (VDD), GF1.209 (VDD), GF1.212 (VDD), GF1.215 (VDD), GF1.217 (VDD), GF1.220 (VDD), GF1.223 (VDD), GF1.226 (VDD), GF1.229 (VDD), GF1.231 (VDD), GF1.233 (VDD), GF1.236 (VDD), R29.2, WAM1.A1 (VDD_1), WAM1.B2 (VDDQ_1), WAM1.B8 (VDDQ_2), WAM1.C1 (VDDQ_3), WAM1.C7 (VDD_2), WAM1.C9 (VDDQ_4), WAM1.E2 (VDDQ_5), WAM1.E8 (VDDQ_6), WAM1.F1 (VDD_3), WAM1.F9 (VDD_4), WAM1.H1 (VDD_5), WAM1.J9 (VDD_6), WAM1.M1 (VDD_7), WAM1.N9 (VDD_8), WAM2.A1 (VDD_1), WAM2.B2 (VDDQ_1), WAM2.B8 (VDDQ_2), WAM2.C1 (VDDQ_3), WAM2.C7 (VDD_2), WAM2.C9 (VDDQ_4), WAM2.E2 (VDDQ_5), WAM2.E8 (VDDQ_6), WAM2.F1 (VDD_3), WAM2.F9 (VDD_4), WAM2.H1 (VDD_5), WAM2.J9 (VDD_6), WAM2.M1 (VDD_7), WAM2.N9 (VDD_8), WAM3.A1 (VDD_1), WAM3.B2 (VDDQ_1), WAM3.B8 (VDDQ_2), WAM3.C1 (VDDQ_3), WAM3.C7 (VDD_2), WAM3.C9 (VDDQ_4), WAM3.E2 (VDDQ_5), WAM3.E8 (VDDQ_6), WAM3.F1 (VDD_3), WAM3.F9 (VDD_4), WAM3.H1 (VDD_5), WAM3.J9 (VDD_6), WAM3.M1 (VDD_7), WAM3.N9 (VDD_8), WAM4.A1 (VDD_1), WAM4.B2 (VDDQ_1), WAM4.B8 (VDDQ_2), WAM4.C1 (VDDQ_3), WAM4.C7 (VDD_2), WAM4.C9 (VDDQ_4), WAM4.E2 (VDDQ_5), WAM4.E8 (VDDQ_6), WAM4.F1 (VDD_3), WAM4.F9 (VDD_4), WAM4.H1 (VDD_5), WAM4.J9 (VDD_6), WAM4.M1 (VDD_7), WAM4.N9 (VDD_8), WAM5.A1 (VDD_1), WAM5.B2 (VDDQ_1), WAM5.B8 (VDDQ_2), WAM5.C1 (VDDQ_3), WAM5.C7 (VDD_2), WAM5.C9 (VDDQ_4), WAM5.E2 (VDDQ_5), WAM5.E8 (VDDQ_6), WAM5.F1 (VDD_3), WAM5.F9 (VDD_4), WAM5.H1 (VDD_5), WAM5.J9 (VDD_6), WAM5.M1 (VDD_7), WAM5.N9 (VDD_8), WAM6.A1 (VDD_1), WAM6.B2 (VDDQ_1), WAM6.B8 (VDDQ_2), WAM6.C1 (VDDQ_3), WAM6.C7 (VDD_2), WAM6.C9 (VDDQ_4), WAM6.E2 (VDDQ_5), WAM6.E8 (VDDQ_6), WAM6.F1 (VDD_3), WAM6.F9 (VDD_4), WAM6.H1 (VDD_5), WAM6.J9 (VDD_6), WAM6.M1 (VDD_7), WAM6.N9 (VDD_8), WAM7.A1 (VDD_1), WAM7.B2 (VDDQ_1), WAM7.B8 (VDDQ_2), WAM7.C1 (VDDQ_3), WAM7.C7 (VDD_2), WAM7.C9 (VDDQ_4), WAM7.E2 (VDDQ_5), WAM7.E8 (VDDQ_6), WAM7.F1 (VDD_3), WAM7.F9 (VDD_4), WAM7.H1 (VDD_5), WAM7.J9 (VDD_6), WAM7.M1 (VDD_7), WAM7.N9 (VDD_8), WAM8.A1 (VDD_1), WAM8.B2 (VDDQ_1), WAM8.B8 (VDDQ_2), WAM8.C1 (VDDQ_3), WAM8.C7 (VDD_2), WAM8.C9 (VDDQ_4), WAM8.E2 (VDDQ_5), WAM8.E8 (VDDQ_6), WAM8.F1 (VDD_3), WAM8.F9 (VDD_4), WAM8.H1 (VDD_5), WAM8.J9 (VDD_6), WAM8.M1 (VDD_7), WAM8.N9 (VDD_8), WAM9.A1 (VDD_1), WAM9.B2 (VDDQ_1), WAM9.B8 (VDDQ_2), WAM9.C1 (VDDQ_3), WAM9.C7 (VDD_2), WAM9.C9 (VDDQ_4), WAM9.E2 (VDDQ_5), WAM9.E8 (VDDQ_6), WAM9.F1 (VDD_3), WAM9.F9 (VDD_4), WAM9.H1 (VDD_5), WAM9.J9 (VDD_6), WAM9.M1 (VDD_7), WAM9.N9 (VDD_8)
VPP: GF1.142 (VPP), GF1.143 (VPP), GF1.286 (VPP), GF1.287 (VPP), GF1.288 (VPP), WAM1.B1 (VPP_1), WAM1.M9 (VPP_2), WAM2.B1 (VPP_1), WAM2.M9 (VPP_2), WAM3.B1 (VPP_1), WAM3.M9 (VPP_2), WAM4.B1 (VPP_1), WAM4.M9 (VPP_2), WAM5.B1 (VPP_1), WAM5.M9 (VPP_2), WAM6.B1 (VPP_1), WAM6.M9 (VPP_2), WAM7.B1 (VPP_1), WAM7.M9 (VPP_2), WAM8.B1 (VPP_1), WAM8.M9 (VPP_2), WAM9.B1 (VPP_1), WAM9.M9 (VPP_2)
VREFCA: GF1.146 (VREFCA), WAM1.J1 (VREFCA), WAM2.J1 (VREFCA), WAM3.J1 (VREFCA), WAM4.J1 (VREFCA), WAM5.J1 (VREFCA), WAM6.J1 (VREFCA), WAM7.J1 (VREFCA), WAM8.J1 (VREFCA), WAM9.J1 (VREFCA)
VTT: GF1.77 (VTT), GF1.221 (VTT), R1.2, R2.2, R3.2, R4.2, R5.2, R6.2, R7.2, R8.2, R9.2, R10.2, R11.2, R12.2, R13.2, R14.2, R15.2, R16.2, R17.2, R18.2, R19.2, R20.2, R21.2, R24.2, R25.2, R26.2, R27.2, R28.2

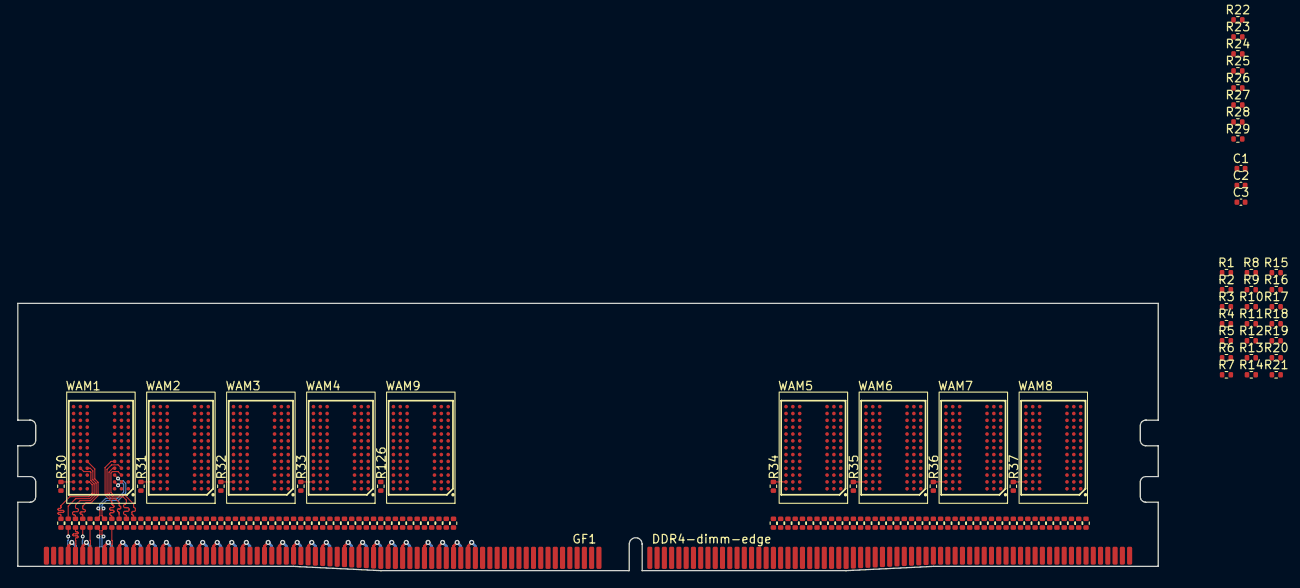
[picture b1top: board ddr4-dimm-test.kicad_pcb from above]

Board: 6 copper layers, 133.3 x 31.2 mm, 150 parts (0 on the bottom side), 243 nets.

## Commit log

2024-10-10 wrote a little readme
2024-10-10 new gitignore
2024-10-10 Update readme lol
2024-10-10 Added ram chip symbol and partial connections
2024-10-10 Connected all common lines and duplicated chip
2024-10-10 Connected data bus
2024-10-10 some component placement
2024-10-11 more component placement
2024-10-13 Some more layout testing
2024-10-13 moved stuff and added line indicating VLP height
2024-10-15 Added ECC?
2024-10-15 do not the ecc
2024-10-15 change cap value
2024-10-16 kangaroo for some reason
2024-10-18 Tried some data bus length matching
2024-10-18 Changed to 6 layer
2024-10-22 Updated DDR4 slot symbol
    gotta show that notch lol
2024-10-30 there's a ddr5 dimm symbol too now
    felt like making it, for future use i guess
2024-11-06 Added link for sodimm edge footprints
2025-05-22 Note about rdimm chip reuse
